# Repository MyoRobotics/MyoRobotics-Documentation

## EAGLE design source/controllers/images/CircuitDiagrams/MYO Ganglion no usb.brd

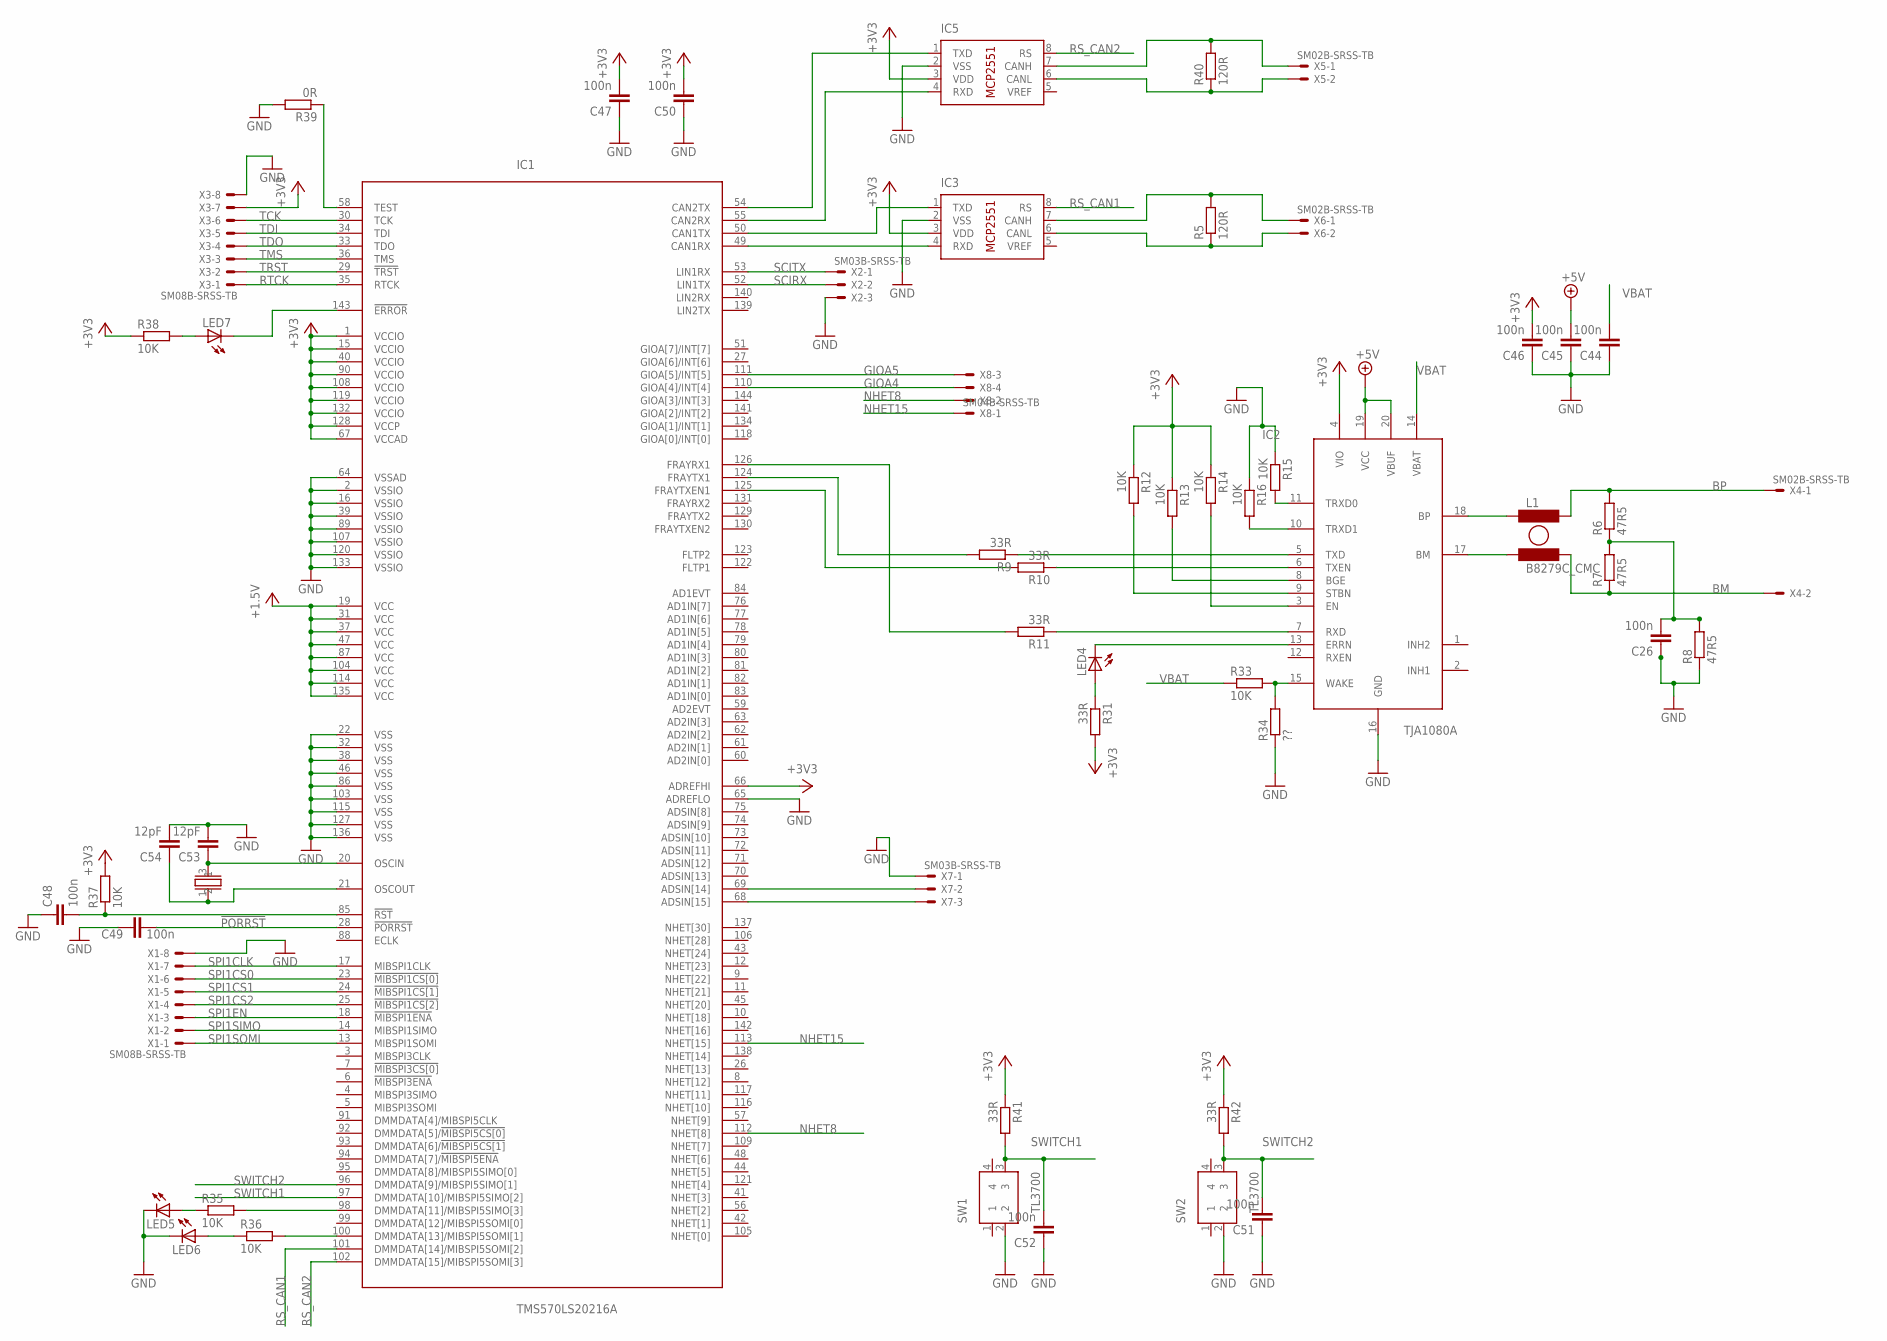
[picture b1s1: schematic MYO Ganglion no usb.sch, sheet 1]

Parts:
C26, C44, C45, C46, C47, C48, C49, C50, C51, C52: 100n; C0402K
C53, C54: 12pF; C0402K
IC1: TMS570LS20216A; PQFP144
IC2: TJA1080A; TSSOP20
IC3, IC5: MCP2551/SN; SO08
L1: B8279C_CMC; 1812CMC
LED4, LED5, LED6, LED7: LEDCHIPLED_0805; CHIPLED_0805
R5, R40: 120R; R0603
R6, R7, R8: 47R5; R0402
R9, R10, R11, R31, R41, R42: 33R; R0402
R12, R13, R14, R15, R16, R33, R35, R36, R37, R38: 10K; R0402
R34: ??; R0402
R39: 0R; R0402
SW1, SW2: TL3700
X1, X3: SM08B-SRSS-TB
X2, X7: SM03B-SRSS-TB
X4, X5, X6: SM02B-SRSS-TB
X8: SM04B-SRSS-TB
XT1: 2.5X2_XTAL

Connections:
!PORRST: C49.2, IC1.28 (!PORRST); also elsewhere on the board
+1V5: IC1.19 (VCC), IC1.31 (VCC), IC1.37 (VCC), IC1.47 (VCC), IC1.87 (VCC), IC1.104 (VCC), IC1.114 (VCC), IC1.135 (VCC); also elsewhere on the board
+3V3: C46.2, C47.2, C50.2, IC1.1 (VCCIO), IC1.15 (VCCIO), IC1.40 (VCCIO), IC1.66 (ADREFHI), IC1.67 (VCCAD), IC1.90 (VCCIO), IC1.108 (VCCIO), IC1.119 (VCCIO), IC1.128 (VCCP), IC1.132 (VCCIO), IC2.4 (VIO), IC3.3 (VDD), IC5.3 (VDD), R12.1, R13.1, R14.1, R31.2, R37.2, R38.1, R41.1, R42.1, X3.7; also elsewhere on the board
+5V: C45.2, IC2.19 (VCC), IC2.20 (VBUF); also elsewhere on the board
BM: L1.4, R7.1, X4.2
BP: L1.2, R6.2, X4.1
GIOA4: IC1.110 (GIOA[4]/INT[4]), X8.4
GIOA5: IC1.111 (GIOA[5]/INT[5]), X8.3
GND: C26.1, C44.1, C45.1, C46.1, C47.1, C48.1, C49.1, C50.1, C51.1, C52.1, C53.2, C54.2, IC1.2 (VSSIO), IC1.16 (VSSIO), IC1.22 (VSS), IC1.32 (VSS), IC1.38 (VSS), IC1.39 (VSSIO), IC1.46 (VSS), IC1.64 (VSSAD), IC1.65 (ADREFLO), IC1.86 (VSS), IC1.89 (VSSIO), IC1.103 (VSS), IC1.107 (VSSIO), IC1.115 (VSS), IC1.120 (VSSIO), IC1.127 (VSS), IC1.133 (VSSIO), IC1.136 (VSS), IC2.16 (GND), IC3.2 (VSS), IC5.2 (VSS), LED5.C, LED6.C, R8.1, R15.1, R16.1, R34.1, R39.2, SW1.2, SW2.2, X1.8, X2.3, X3.8, X7.1; also elsewhere on the board
unnamed: IC2.18 (BP), L1.1
unnamed: IC1.50 (CAN1TX), IC3.1 (TXD)
unnamed: IC1.49 (CAN1RX), IC3.4 (RXD)
unnamed: IC2.17 (BM), L1.3
unnamed: C53.1, IC1.20 (OSCIN), XT1.3 (2)
unnamed: C54.1, IC1.21 (OSCOUT), XT1.1
unnamed: IC3.7 (CANH), R5.2, X6.1
unnamed: IC3.6 (CANL), R5.1, X6.2
unnamed: IC2.5 (TXD), R9.1
unnamed: IC2.6 (TXEN), R10.1
unnamed: IC1.98 (DMMDATA[11]/MIBSPI5SIMO[3]), R35.2
unnamed: IC1.100 (DMMDATA[13]/MIBSPI5SOMI[1]), R36.2
unnamed: IC2.7 (RXD), R11.1
unnamed: C26.2, R6.1, R7.2, R8.2
unnamed: IC2.9 (STBN), R12.2
unnamed: IC2.8 (BGE), R13.2
unnamed: IC2.3 (EN), R14.2
unnamed: IC1.68 (ADSIN[15]), X7.3
unnamed: IC1.69 (ADSIN[14]), X7.2
unnamed: IC2.11 (TRXD0), R15.2
unnamed: IC2.10 (TRXD1), R16.2
unnamed: IC1.126 (FRAYRX1), R11.2
unnamed: IC1.124 (FRAYTX1), R9.2
unnamed: IC1.125 (FRAYTXEN1), R10.2
unnamed: LED4.A, R31.1
unnamed: IC2.13 (ERRN), LED4.C
unnamed: IC2.15 (WAKE), R33.2, R34.2
unnamed: LED5.A, R35.1
unnamed: LED6.A, R36.1
unnamed: IC1.54 (CAN2TX), IC5.1 (TXD)
unnamed: C48.2, IC1.85 (!RST), R37.1
unnamed: IC1.58 (TEST), R39.1
unnamed: IC1.143 (!ERROR), LED7.C
unnamed: LED7.A, R38.2
unnamed: IC1.55 (CAN2RX), IC5.4 (RXD)
unnamed: IC5.7 (CANH), R40.2, X5.1
unnamed: IC5.6 (CANL), R40.1, X5.2
NHET8: IC1.112 (NHET[8]), X8.2
NHET15: IC1.113 (NHET[15]), X8.1
RS_CAN1: IC1.101 (DMMDATA[14]/MIBSPI5SOMI[2]), IC3.8 (RS)
RS_CAN2: IC1.102 (DMMDATA[15]/MIBSPI5SOMI[3]), IC5.8 (RS)
RTCK: IC1.35 (RTCK), X3.1
SCIRX: IC1.52 (LIN1TX), X2.2
SCITX: IC1.53 (LIN1RX), X2.1
SPI1CLK: IC1.17 (MIBSPI1CLK), X1.7
SPI1CS0: IC1.23 (!MIBSPI1CS[0]), X1.6
SPI1CS1: IC1.24 (!MIBSPI1CS[1]), X1.5
SPI1CS2: IC1.25 (!MIBSPI1CS[2]), X1.4
SPI1EN: IC1.18 (!MIBSPI1ENA), X1.3
SPI1SIMO: IC1.14 (MIBSPI1SIMO), X1.2
SPI1SOMI: IC1.13 (MIBSPI1SOMI), X1.1
SWITCH1: C52.2, IC1.97 (DMMDATA[10]/MIBSPI5SIMO[2]), R41.2, SW1.3
SWITCH2: C51.2, IC1.96 (DMMDATA[9]/MIBSPI5SIMO[1]), R42.2, SW2.3
TCK: IC1.30 (TCK), X3.6
TDI: IC1.34 (TDI), X3.5
TDO: IC1.33 (TDO), X3.4
TMS: IC1.36 (TMS), X3.3
TRST: IC1.29 (!TRST), X3.2
VBAT: C44.2, IC2.14 (VBAT), R33.1; also elsewhere on the board

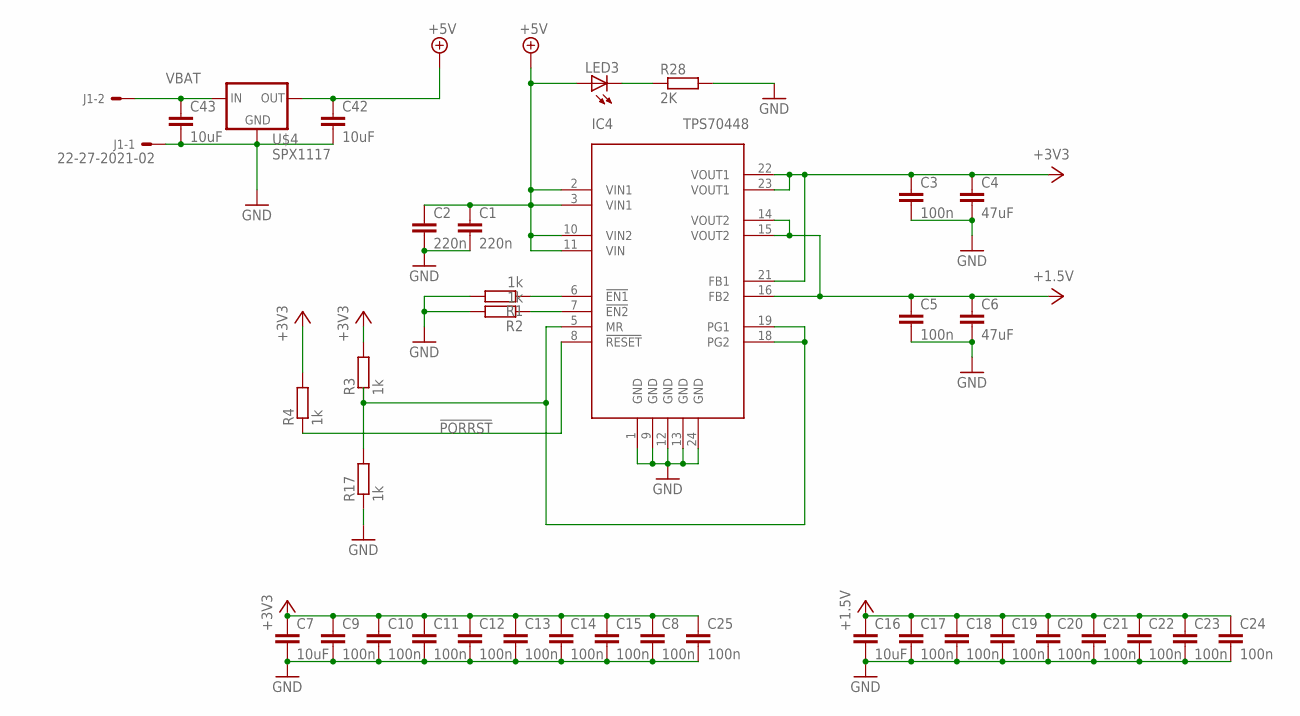
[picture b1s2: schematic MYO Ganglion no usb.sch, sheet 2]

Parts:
C1, C2: 220n; C0402K
C3, C5, C8, C9, C10, C11, C12, C13, C14, C15, C17, C18, C19, C20, C21, C22, C23, C24, C25: 100n; C0402K
C4, C6: 47uF; C0805K
C7, C16, C42, C43: 10uF; C0805K
IC4: TPS70448; HTSSOP24PWP
J1: 22-27-2021-02; 6410-02
LED3: LEDCHIPLED_0805; CHIPLED_0805
R1, R2, R3, R4, R17: 1k; R0402
R28: 2K; R0402
U$4: SPX1117; SOT223

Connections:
!PORRST: IC4.8 (!RESET), R4.1; also elsewhere on the board
+1V5: C5.1, C6.1, C16.1, C17.1, C18.1, C19.1, C20.1, C21.1, C22.1, C23.1, C24.1, IC4.14 (VOUT2), IC4.15 (VOUT2), IC4.16 (FB2); also elsewhere on the board
+3V3: C3.1, C4.1, C7.1, C8.1, C9.1, C10.1, C11.1, C12.1, C13.1, C14.1, C15.1, C25.1, IC4.21 (FB1), IC4.22 (VOUT1), IC4.23 (VOUT1), R3.2, R4.2; also elsewhere on the board
+5V: C1.1, C2.1, C42.1, IC4.2 (VIN1), IC4.3 (VIN1), IC4.10 (VIN2), IC4.11 (VIN), LED3.A, U$4.2 (OUT); also elsewhere on the board
GND: C1.2, C2.2, C3.2, C4.2, C5.2, C6.2, C7.2, C8.2, C9.2, C10.2, C11.2, C12.2, C13.2, C14.2, C15.2, C16.2, C17.2, C18.2, C19.2, C20.2, C21.2, C22.2, C23.2, C24.2, C25.2, C42.2, C43.2, IC4.1 (GND), IC4.9 (GND), IC4.12 (GND), IC4.13 (GND), IC4.24 (GND), J1.1, R1.2, R2.2, R17.1, R28.2, U$4.1 (GND); also elsewhere on the board
unnamed: IC4.6 (!EN1), R1.1
unnamed: IC4.7 (!EN2), R2.1
unnamed: IC4.5 (MR), IC4.18 (PG2), IC4.19 (PG1), R3.1, R17.2
unnamed: LED3.C, R28.1
VBAT: C43.1, J1.2, U$4.3 (IN); also elsewhere on the board

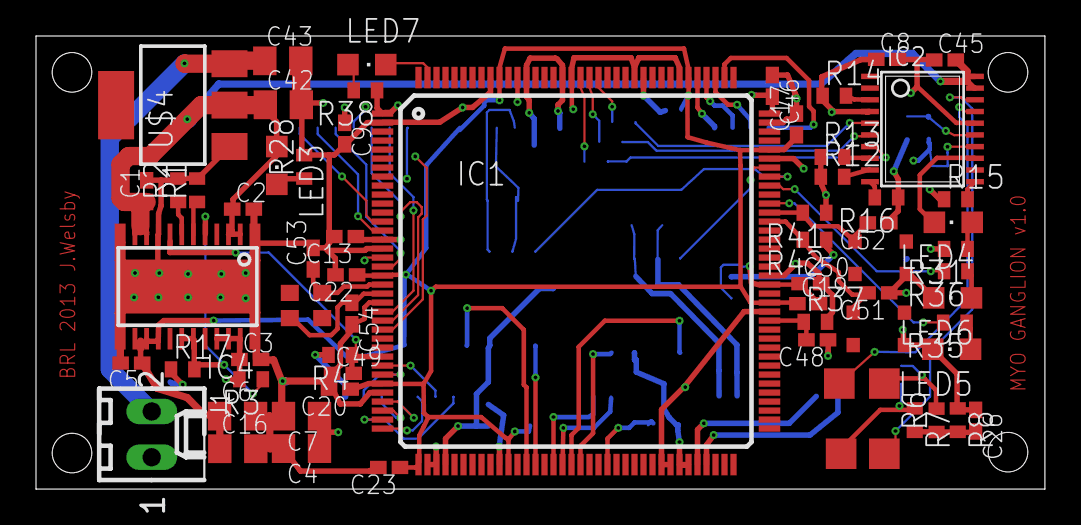
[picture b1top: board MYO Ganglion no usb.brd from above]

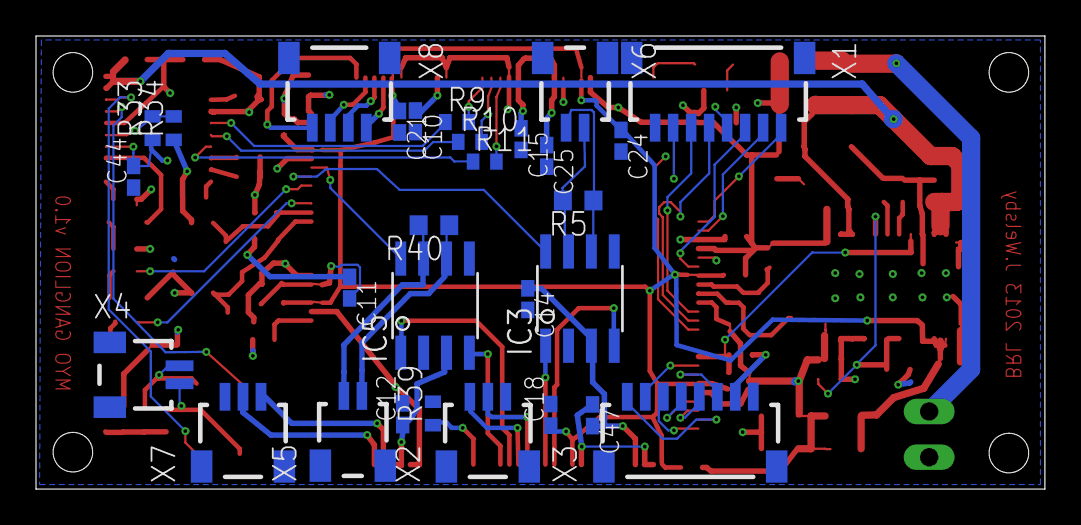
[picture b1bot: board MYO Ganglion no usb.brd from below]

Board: 4 copper layers, 56.0 x 25.2 mm, 92 parts (29 on the bottom side), 72 nets.

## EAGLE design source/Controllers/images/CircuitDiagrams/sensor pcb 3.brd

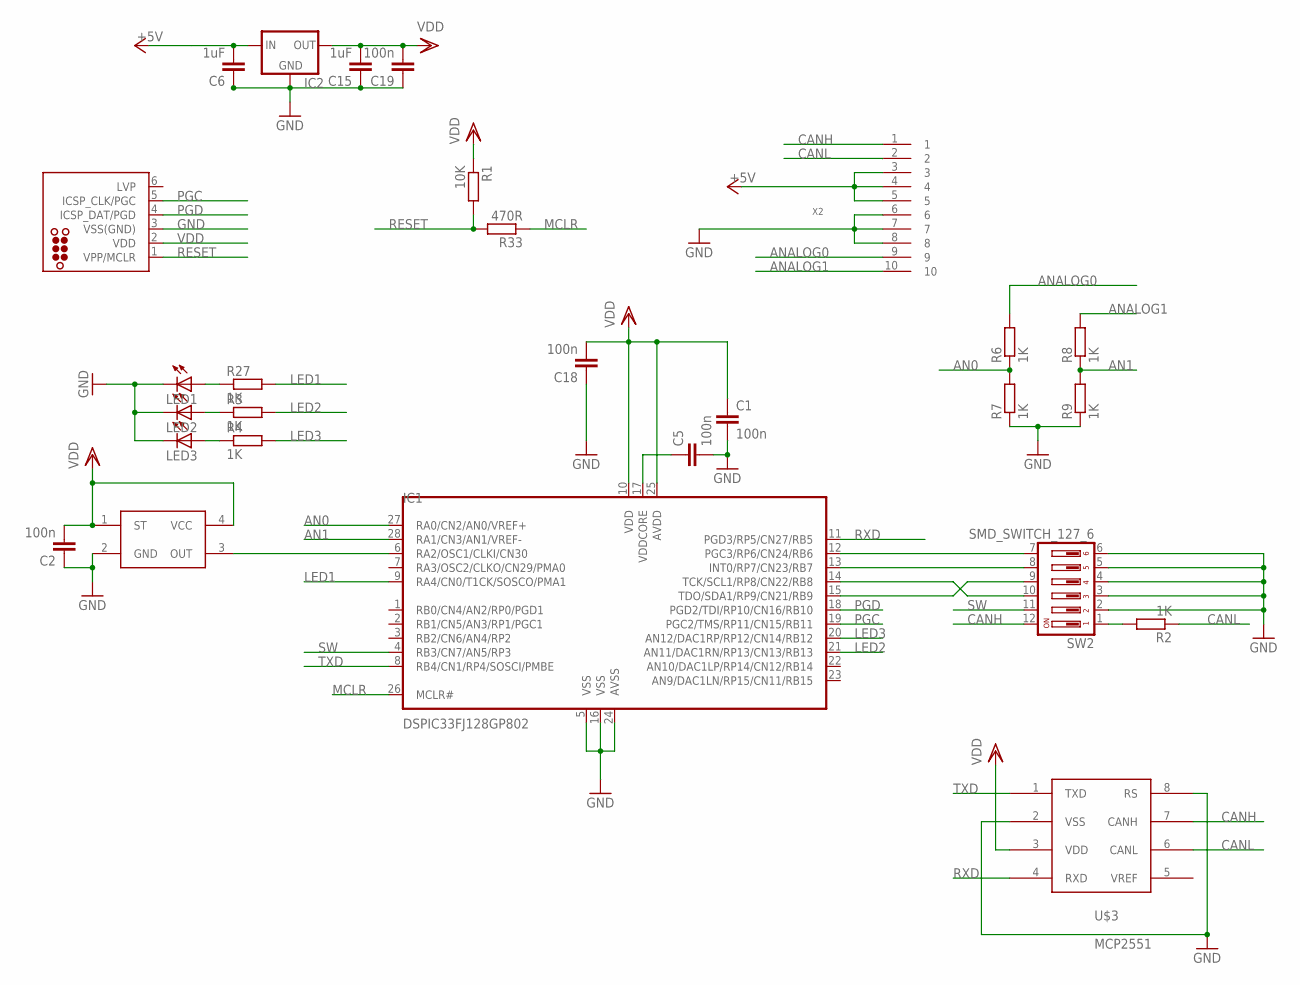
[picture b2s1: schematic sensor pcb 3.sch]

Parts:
C1, C2, C5, C18, C19: 100n; C0402K
C6, C15: 1uF; C0402K
IC1: DSPIC33FJ128GP802; QFN-S28-6X6
IC2: XC63FPM; SOT23
J1: TC2030-MCP-NL
LED1, LED2, LED3: LEDCHIPLED_0603; CHIPLED_0603
R1: 10K; R0402
R2, R3, R4, R6, R7, R8, R9, R27: 1K; R0402
R33: 470R; R0402
SW2: SMD_SWITCH_127_6
U$1: SG-310
U$3: MCP2551; 999
X2: 10PINJAS; 10PIN0.1

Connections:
+5V: C6.2, IC2.3 (IN), X2.3, X2.4, X2.5
AN0: IC1.27 (RA0/CN2/AN0/VREF+), R6.1, R7.2
AN1: IC1.28 (RA1/CN3/AN1/VREF-), R8.1, R9.2
ANALOG0: R6.2, X2.9
ANALOG1: R8.2, X2.10
CANH: SW2.12, U$3.7 (CANH), X2.1
CANL: R2.1, U$3.6 (CANL), X2.2
GND: C1.2, C2.1, C5.2, C6.1, C15.1, C18.1, C19.1, IC1.5 (VSS), IC1.16 (VSS), IC1.24 (AVSS), IC2.1 (GND), J1.3 (VSS(GND)), LED1.C, LED2.C, LED3.C, R7.1, R9.1, SW2.2, SW2.3, SW2.4, SW2.5, SW2.6, U$1.2 (GND), U$3.2 (VSS), U$3.8 (RS), X2.6, X2.7, X2.8
LED1: IC1.9 (RA4/CN0/T1CK/SOSCO/PMA1), R27.2
LED2: IC1.21 (AN11/DAC1RN/RP13/CN13/RB13), R3.2
LED3: IC1.20 (AN12/DAC1RP/RP12/CN14/RB12), R4.2
MCLR: IC1.26 (MCLR#), R33.1
unnamed: IC1.12 (PGC3/RP6/CN24/RB6), SW2.7
unnamed: IC1.13 (INT0/RP7/CN23/RB7), SW2.8
unnamed: IC1.15 (TDO/SDA1/RP9/CN21/RB9), SW2.9
unnamed: IC1.14 (TCK/SCL1/RP8/CN22/RB8), SW2.10
unnamed: IC1.6 (RA2/OSC1/CLKI/CN30), U$1.3 (OUT)
unnamed: C5.1, IC1.17 (VDDCORE)
unnamed: R2.2, SW2.1
unnamed: LED2.A, R3.1
unnamed: LED3.A, R4.1
unnamed: LED1.A, R27.1
PGC: IC1.19 (PGC2/TMS/RP11/CN15/RB11), J1.5 (ICSP_CLK/PGC)
PGD: IC1.18 (PGD2/TDI/RP10/CN16/RB10), J1.4 (ICSP_DAT/PGD)
RESET: J1.1 (VPP/MCLR), R1.2, R33.2
RXD: IC1.11 (PGD3/RP5/CN27/RB5), U$3.4 (RXD)
SW: IC1.4 (RB3/CN7/AN5/RP3), SW2.11
TXD: IC1.8 (RB4/CN1/RP4/SOSCI/PMBE), U$3.1 (TXD)
VDD: C1.1, C2.2, C15.2, C18.2, C19.2, IC1.10 (VDD), IC1.25 (AVDD), IC2.2 (OUT), J1.2 (VDD), R1.1, U$1.1 (ST), U$1.4 (VCC), U$3.3 (VDD)

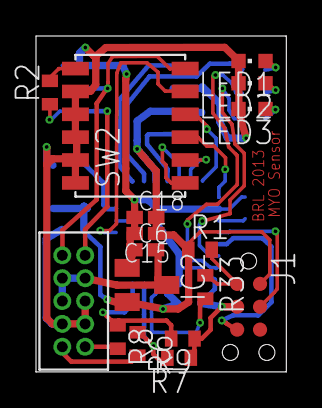
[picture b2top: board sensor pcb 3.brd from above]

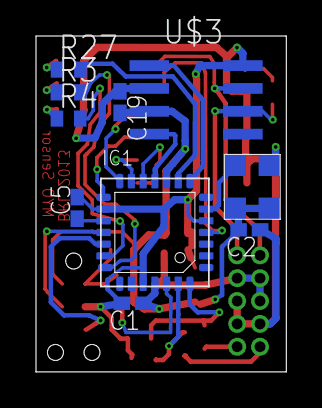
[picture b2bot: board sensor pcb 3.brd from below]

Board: 2 copper layers, 13.9 x 18.7 mm, 27 parts (10 on the bottom side), 29 nets.

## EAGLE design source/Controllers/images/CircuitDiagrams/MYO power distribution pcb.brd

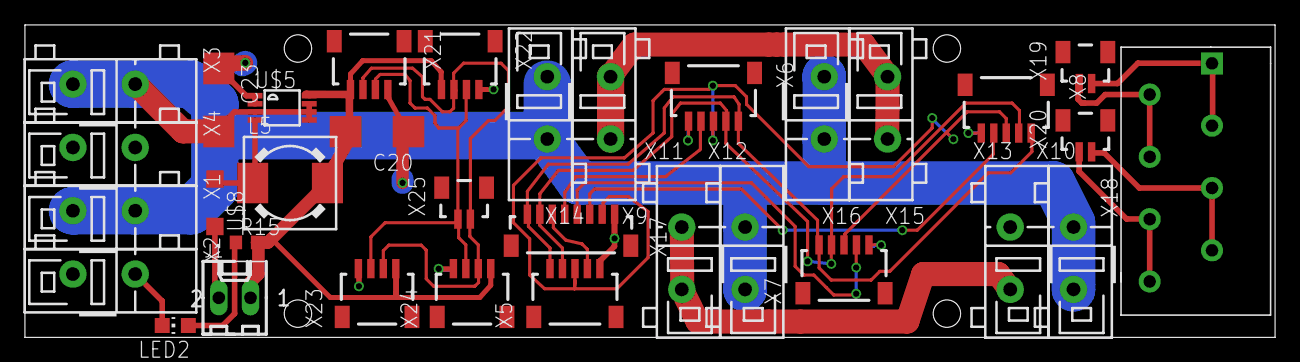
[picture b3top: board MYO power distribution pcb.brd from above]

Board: 2 copper layers, 100.3 x 25.1 mm, 33 parts (0 on the bottom side), 18 nets.

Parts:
C20, C23: C/6032-28R
J1: 22-27-2021-02; 6410-02
L5: DR73
LED2: CHIP-LED0805
R15: 1k; R0603
U$5: MAX1776; UMAX8
U$8: 1N5819HW; SOD123
X1, X2, X3, X4, X9, X10, X11, X12, X13, X14, X15, X16: 236-740-5,08; 236-4XX
X5, X6, X7, X8: SM05B-SRSS-TB
X17: BM08B-SRSS-TB
X18: CON_PTSA_8; PHOENIX_PSTA_8
X19, X20, X25: BM02B-SRSS-TB
X21, X22, X23, X24: SM04B-SRSS-TB

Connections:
+5V: C20.+, J1.1, L5.2, R15.2, U$5.8, X21.4, X22.4, X23.4, X24.4
CANH: X21.3, X22.3, X23.3, X24.3, X25.1
CANL: X21.2, X22.2, X23.2, X24.2, X25.2
F1+: X18.1, X18.3, X19.1
F1-: X18.2, X18.4, X19.2
F2+: X18.5, X18.7, X20.1
F2-: X18.6, X18.8, X20.2
GND: C20.-, C23.-, J1.2, LED2.C, U$5.1, U$5.2, U$8.A, X2.1@1, X2.1@2, X4.1@1, X4.1@2, X5.5, X6.5, X7.5, X8.5, X9.1@1, X9.1@2, X11.1@1, X11.1@2, X13.1@1, X13.1@2, X15.1@1, X15.1@2, X17.8, X21.1, X22.1, X23.1, X24.1
unnamed: LED2.A, R15.1
unnamed: L5.1, U$5.4, U$8.C
SPI1CLK: X5.3, X6.3, X7.3, X8.3, X17.7
SPI1CS0: X8.4, X17.6
SPI1CS1: X7.4, X17.5
SPI1CS2: X6.4, X17.4
SPI1CS3: X5.4, X17.3
SPI1SIMO: X5.2, X6.2, X7.2, X8.2, X17.2
SPI1SOMI: X5.1, X6.1, X7.1, X8.1, X17.1
V+: C23.+, U$5.3, U$5.5, U$5.6, U$5.7, X1.1@1, X1.1@2, X3.1@1, X3.1@2, X10.1@1, X10.1@2, X12.1@1, X12.1@2, X14.1@1, X14.1@2, X16.1@1, X16.1@2

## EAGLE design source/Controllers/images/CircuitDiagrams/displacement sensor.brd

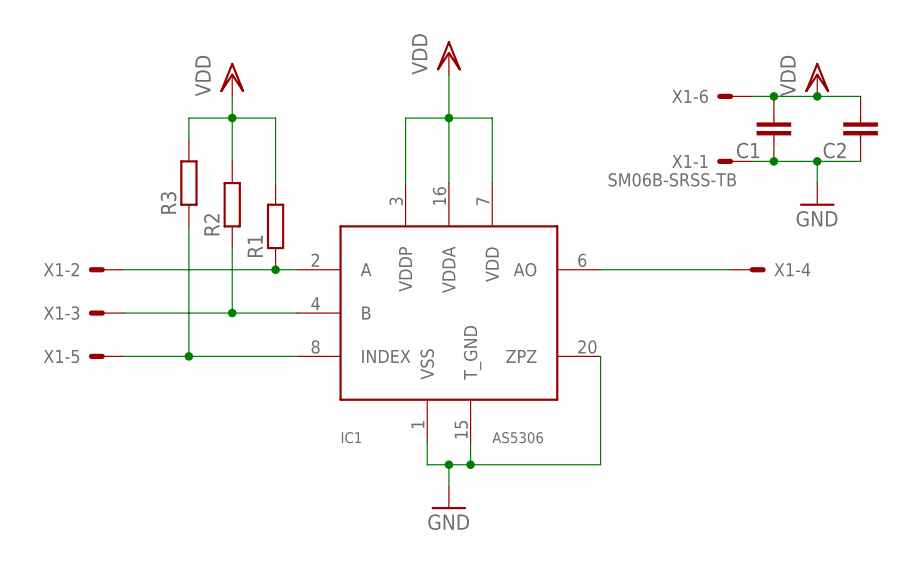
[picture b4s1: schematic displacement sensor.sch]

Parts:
C1, C2: C-EUC0402K; C0402K
IC1: AS5306; TSSOP20
R1, R2, R3: R-EU_R0402; R0402
X1: SM06B-SRSS-TB

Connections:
GND: C1.1, C2.1, IC1.1 (VSS), IC1.15 (T_GND), IC1.20 (ZPZ), X1.1
unnamed: IC1.6 (AO), X1.4
unnamed: IC1.2 (A), R1.1, X1.2
unnamed: IC1.4 (B), R2.1, X1.3
unnamed: IC1.8 (INDEX), R3.1, X1.5
VDD: C1.2, C2.2, IC1.3 (VDDP), IC1.7 (VDD), IC1.16 (VDDA), R1.2, R2.2, R3.2, X1.6

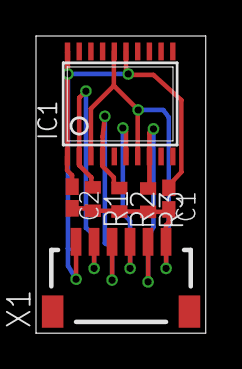
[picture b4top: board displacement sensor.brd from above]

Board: 2 copper layers, 9.4 x 16.5 mm, 7 parts (0 on the bottom side), 6 nets.

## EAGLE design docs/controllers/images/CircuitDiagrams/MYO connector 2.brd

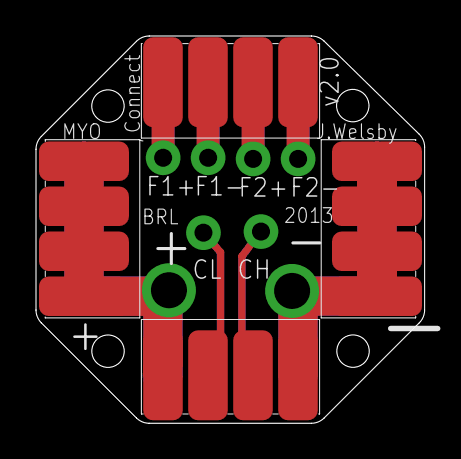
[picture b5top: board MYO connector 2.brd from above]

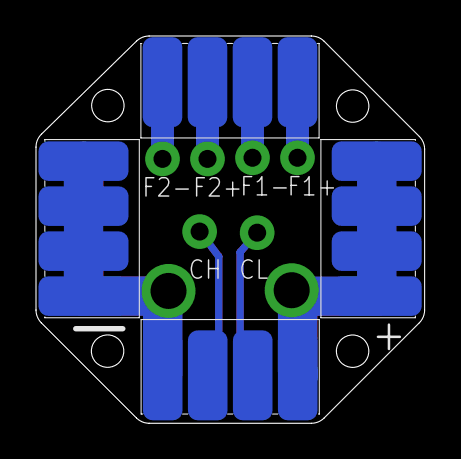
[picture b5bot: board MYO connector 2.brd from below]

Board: 2 copper layers, 21.6 x 21.5 mm, 8 parts (4 on the bottom side), 8 nets.

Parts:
J1, J2, J3, J4, J5, J6, J7, J8: 4WAY_BATTERY_CON; 4-WAY-BATTERY_CON

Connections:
CH: J3.2, J7.3
CL: J3.3, J7.2
F1+: J4.1, J8.4
F1-: J4.2, J8.3
F2+: J4.3, J8.2
F2-: J4.4, J8.1
GND: J2.1, J2.2, J2.3, J2.4, J3.1, J6.1, J6.2, J6.3, J6.4, J7.4
VDD: J1.1, J1.2, J1.3, J1.4, J3.4, J5.1, J5.2, J5.3, J5.4, J7.1

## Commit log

2017-02-14 Disable githubpages plugin as its not supported by read the docs
2017-02-14 Add rtd theme
2017-02-14 Structure, add installation instructions
2017-02-14 Fix indentation
2017-02-14 Bugfix on code-blocks
2017-02-14 Add small overview of order of website
2017-02-14 Fix license of documentatioN
2017-03-22 Add Electronics
2017-03-22 Enable numfig plugin
2017-03-22 Tables and Figure
2017-03-22 Added images
2017-03-23 Images fixed
2017-03-23 Final changes
2017-03-23 small changes
2017-03-23 Changes to Controllers
2017-03-27 Add dependencies installation
2017-03-27 Addendum to last commit due to bugfix
2017-03-29 images now hopefully work
2017-03-29 No image name duplicate
2017-03-29 underscore removed
2017-03-29 changed figure directory
2017-03-29 renamed figures again
2017-03-29 renamed images again again
2017-03-29 images
2017-03-29 more image stuff
2017-03-29 final image
2017-03-29 D4.1 completed
2017-03-29 assembly first changes
2017-03-30 Updated Index with Assembly
2017-03-30 started working on Assembly
2017-04-04 Assembly changes
2017-04-05 (nearly) final D3.4 changes
2017-04-06 Final Changes to D3.4
2017-04-06 final final changes
2017-04-06 Amendments to step 2 of muscle
2017-04-06 Amendments to step 3 and 4
2017-04-06 Amendments to step 6
2017-04-06 Amendments to setep 7,8,9
2017-04-06 Added heading to steps
2017-04-06 Amendements to the asymetric joint
2017-04-06 Updated Partners
2017-04-06 Refer to the orga repositories
    My changes on [flexrayusbinterface](https://github.com/Roboy/flexrayusbinterface/tree/develop) and [myo_blink](https://github.com/Roboy/myo_blink) were already merged into the original [Roboy organiz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
2017-04-06 Amendments to the wires and adding of muscle table
2017-04-10 Typos and deleted sentences that made no sense
2017-04-12 Added aligni tables
2017-04-12 small changes 2
2017-05-01 Add all new ganglion mounting options
2017-05-03 Reordering and breaking into small files
2017-05-03 Add captions to muscle assembly
2017-05-03 Reformat J22 assembly instructions
2017-05-03 Restructure bone assembly
2017-05-03 Add applications section with MyoArm
2017-05-24 Move getting started to myo_blink
2017-05-24 Fix list in getting_started
2017-05-24 Fixed the missing instructions for installing the udev rules
2017-05-29 Add instructions to configure serial number of USB2Flexray adapter in the myo_blink yaml file
2017-05-29 Add note to also configure serial for ros_control_boilerplate
2017-05-29 Improve the usb serial search description
2017-05-29 Add user to group dialout'
2017-05-29 Code-block rendering as bash
2017-05-29 Add roscd and add missing sudo to install_udev_rules.sh
2017-05-29 Add troubleshooting section
2017-05-29 Bugfix: newline before code-block directive
2017-05-31 Fix wrong myo_blink call example
2017-06-01 Move terminator note into its own part
2024-04-21 Documentation with correct copyright and no license
2024-04-21 Upgraded to new RTD version

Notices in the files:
parts and their libraries:
tag-connect: ©2009 ROFA.cz - modified and updated by Robert Darlington ‹rdarlington@gmail.com›
